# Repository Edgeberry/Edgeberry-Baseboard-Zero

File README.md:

The **Edgeberry Zero** provides essential additional functionality for deploying the Raspberry Pi Zero as an IoT edge device in a real-world environment.

- **12 to 24VDC input power supply** for reliably powering the device with up to 3A at 5V.
- **Indicators and button** for providing status feedback and device interaction
- **Expansion slot** for application-specific Edgeberry Hardware Cartridges
- **Robust enclosure** for withstanding the environmental challenges of the real world

<br/>
<br clear="right"/>

## Edgeberry Device Software
For using your Edgeberry hardware with the Edgeberry ecosystem (e.g. the Edgeberry Dashboard), you'll need to install the [Edgeberry Device Software](https://github.com/Edgeberry/Edgeberry/). Follow [these installation steps](https://github.com/Edgeberry/Edgeberry?tab=readme-ov-file#installation). If you have different plans with this board, this software is not required for correct operation of any of its hardware components.

## Enclosure
The enclosure, designed in FreeCAD, protects the device from the challenges of the physical world.

1) Faceplate front
2) Enclosure
3) Faceplate back
4) Sticker
5) Mounting groove

<br clear="left"/>

## (re)Writing the EEPROM
>[!important]
>**When you purchased the Edgeberry Hardware, the manufacturer has written the EEPROM**. If you are the manufacturer, or you're hacking your Edgeberry board, then continue with the following steps.

1) Close the `write protection` jumper (JP1) on the Edgeberry Hardware to enable writing the EEPROM
2) Download and build the [Raspberry Pi Hat eeprom utils](https://github.com/raspberrypi/hats) on your device 
3) Make the EEPROM file from the eeprom_settings.txt using `eepmake` <br> e.g. `$ ./eepmake eeprom_settings.txt edgeberry.eep`
4) Flash the EEPROM using `eepflash.sh` <br> e.g. `$ sudo ./eepflash -w -t=24c256 -f=edgeberry.eep`
5) Now `reboot` the device and check the device tree for your hat's settings <br> e.g. `$ cat /proc/device-tree/hat/vendor`)

## License & Collaboration
**Copyright© 2025 Sanne 'SpuQ' Santens**. This project is released under the [**CERN OHL-W**](./LICENSE.txt) license. The [Rules & Guidelines](https://github.com/Edgeberry/.github/blob/main/brand/Edgeberry_Trademark_Rules_and_Guidelines.md) apply to the usage of the Edgeberry™ brand.

### Collaboration

If you'd like to contribute to this project, please follow these guidelines:
1. Fork the repository and create your branch from `main`.
2. Make your changes and ensure they adhere to the project's design style and conventions.
3. Test your changes thoroughly.
4. Ensure your commits are descriptive and well-documented.
5. Open a pull request, describing the changes you've made and the problem or feature they address.

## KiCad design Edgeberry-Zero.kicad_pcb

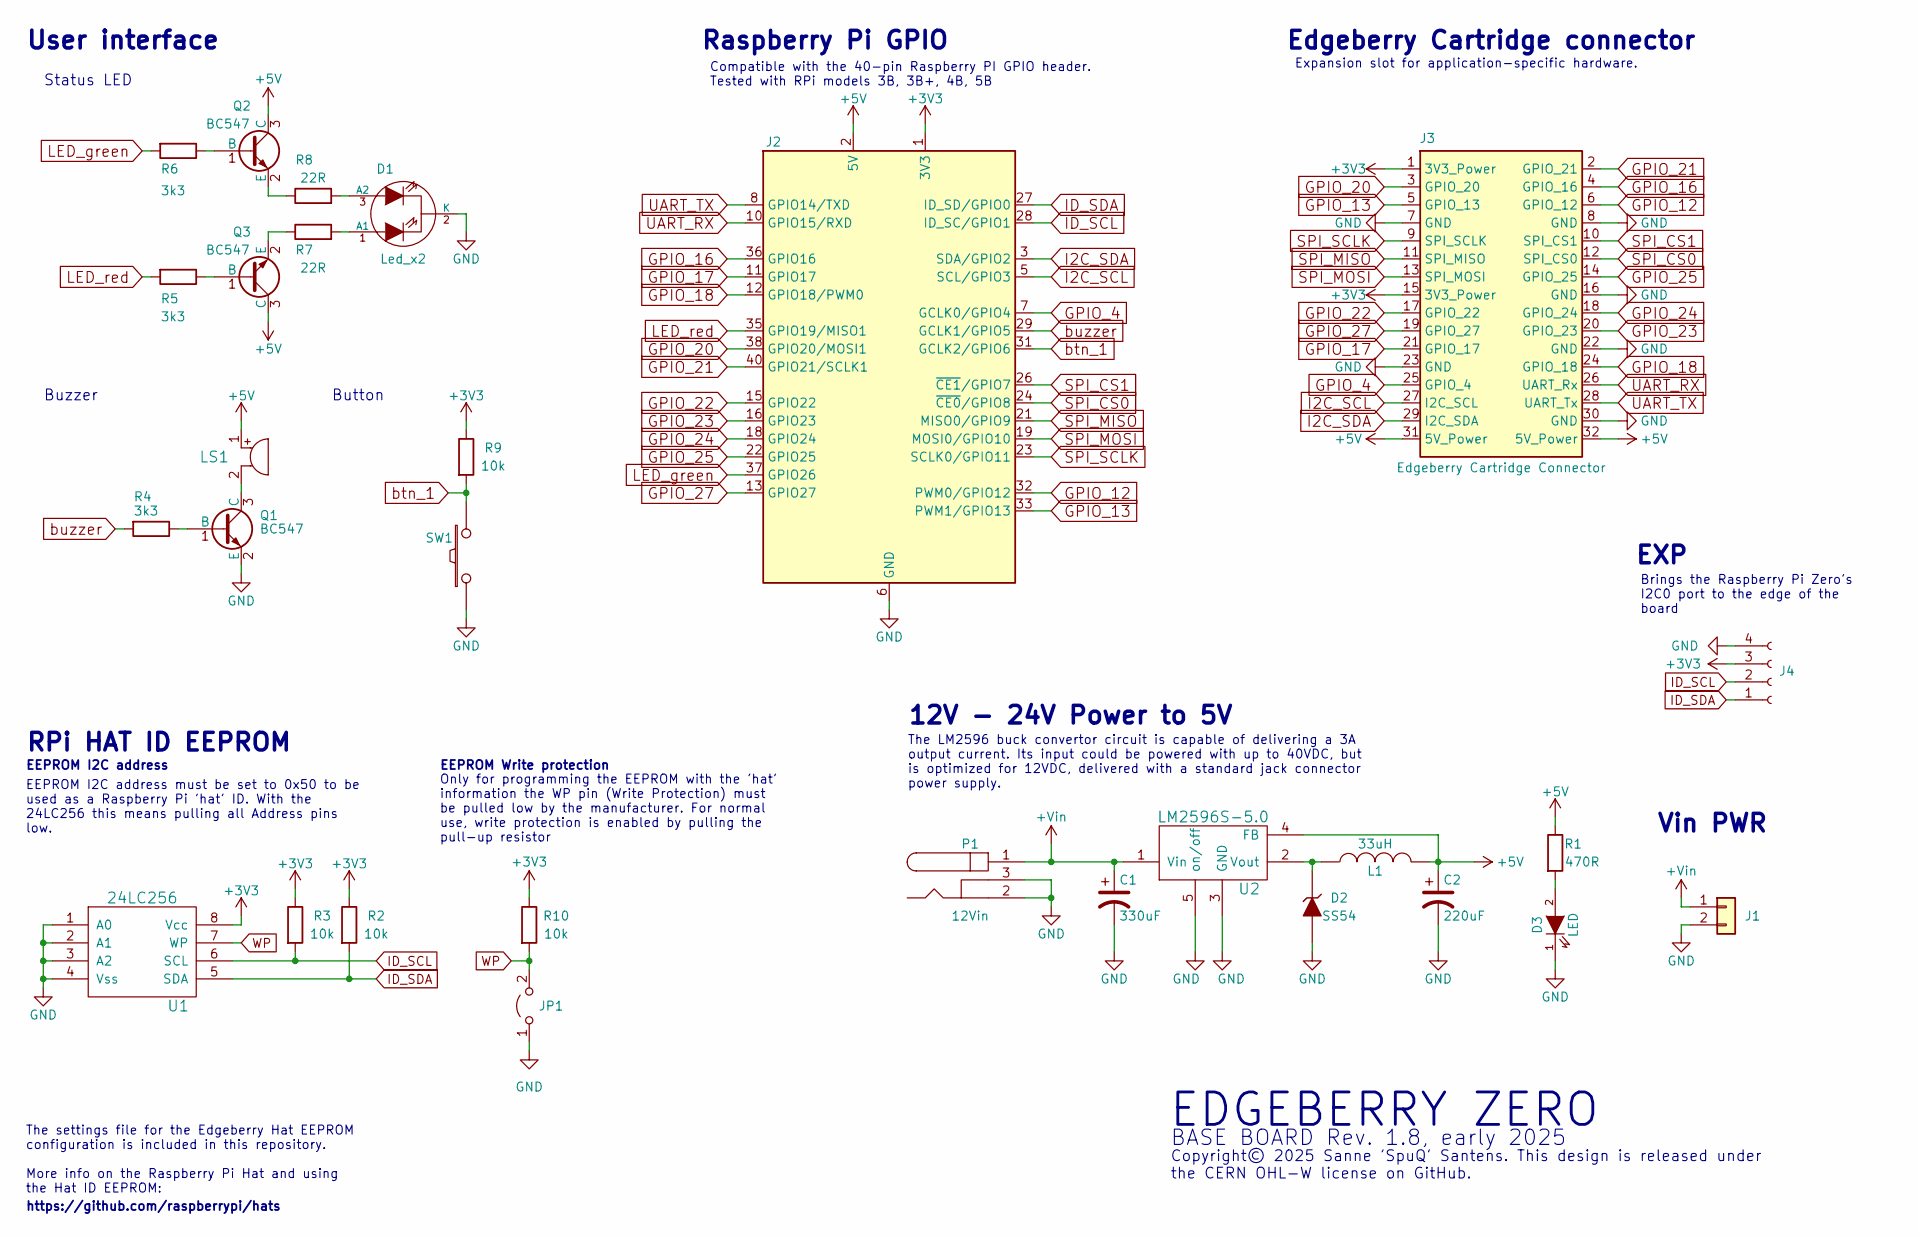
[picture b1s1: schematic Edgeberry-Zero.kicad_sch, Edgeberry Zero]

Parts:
C1: 330uF; c_elec_8x10
C2: 220uF; c_elec_8x10
D1: Led_x2; bicolor_LED_right_angle
D2: SS54; D_SMA
D3: LED; LED_0805_2012Metric
J1: Molex_KK_1x02_P2.54mm; Molex_KK-254_AE-6410-02A_1x02_P2.54mm_Vertical
J2: Raspberry_Pi_2_3; PinSocket_2x20_P2.54mm_Vertical
J3: Edgeberry Cartridge Connector; PinSocket_2x16_P2.54mm_Horizontal
J4: Conn_01x04_Socket; PinSocket_1x04_P2.00mm_Horizontal
JP1: Jumper_2_Open; PinHeader_1x02_P2.54mm_Vertical
L1: 33uH; SELF-WE-PD-XXL
LS1: Buzzer; Buzzer_12x9.5RM7.6
P1: 12Vin; BarrelJack_Horizontal
Q1, Q2, Q3: BC547; SOT-23
R1: 470R; R_0805_2012Metric
R2, R3, R9, R10: 10k; R_0805_2012Metric
R4, R5, R6: 3k3; R_0805_2012Metric
R7, R8: 22R; R_0805_2012Metric
SW1: SW_PUSH; tactile_switch_vertical
U1: 24LC256; SOIC_8
U2: LM2596S-5.0; TO-263-5_TabPin3

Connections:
+3V3: J2.1 (3V3), J2.17 (3V3), J3.1 (3V3_Power), J3.15 (3V3_Power), J4.3, R2.1, R3.1, R9.1, R10.1, U1.8 (Vcc)
+5V: C2.1, J2.2 (5V), J2.4 (5V), J3.31 (5V_Power), J3.32 (5V_Power), L1.2, LS1.1, Q2.3 (C), Q3.3 (C), R1.1, U2.4 (FB)
+Vin: C1.1, J1.1, P1.1, U2.1 (Vin)
GND: C1.2, C2.2, D1.2 (K), D2.2 (A), D3.1 (K), J1.2, J2.6 (GND), J2.9 (GND), J2.14 (GND), J2.20 (GND), J2.25 (GND), J2.30 (GND), J2.34 (GND), J2.39 (GND), J3.7 (GND), J3.8 (GND), J3.16 (GND), J3.22 (GND), J3.23 (GND), J3.30 (GND), J4.4, JP1.1 (A), P1.2, P1.3, Q1.2 (E), SW1.1, U1.1 (A0), U1.2 (A1), U1.3 (A2), U1.4 (Vss), U2.3 (GND), U2.5 (on/off)
GPIO_4: J2.7 (GCLK0/GPIO4), J3.25 (GPIO_4)
GPIO_12: J2.32 (PWM0/GPIO12), J3.6 (GPIO_12)
GPIO_13: J2.33 (PWM1/GPIO13), J3.5 (GPIO_13)
GPIO_16: J2.36 (GPIO16), J3.4 (GPIO_16)
GPIO_17: J2.11 (GPIO17), J3.21 (GPIO_17)
GPIO_18: J2.12 (GPIO18/PWM0), J3.24 (GPIO_18)
GPIO_20: J2.38 (GPIO20/MOSI1), J3.3 (GPIO_20)
GPIO_21: J2.40 (GPIO21/SCLK1), J3.2 (GPIO_21)
GPIO_22: J2.15 (GPIO22), J3.17 (GPIO_22)
GPIO_23: J2.16 (GPIO23), J3.20 (GPIO_23)
GPIO_24: J2.18 (GPIO24), J3.18 (GPIO_24)
GPIO_25: J2.22 (GPIO25), J3.14 (GPIO_25)
GPIO_27: J2.13 (GPIO27), J3.19 (GPIO_27)
I2C_SCL: J2.5 (SCL/GPIO3), J3.27 (I2C_SCL)
I2C_SDA: J2.3 (SDA/GPIO2), J3.29 (I2C_SDA)
ID_SCL: J2.28 (ID_SC/GPIO1), J4.2, R3.2, U1.6 (SCL)
ID_SDA: J2.27 (ID_SD/GPIO0), J4.1, R2.2, U1.5 (SDA)
LED_green: J2.37 (GPIO26), R6.2
LED_red: J2.35 (GPIO19/MISO1), R5.2
unnamed: D1.1 (A1), R7.2
unnamed: D1.3 (A2), R8.2
unnamed: D2.1 (K), L1.1, U2.2 (Vout)
unnamed: D3.2 (A), R1.2
unnamed: Q1.1 (B), R4.1
unnamed: LS1.2, Q1.3 (C)
unnamed: Q2.1 (B), R6.1
unnamed: Q2.2 (E), R8.1
unnamed: Q3.1 (B), R5.1
unnamed: Q3.2 (E), R7.1
SPI_CS0: J2.24 (~CE0/GPIO8), J3.12 (SPI_CS0)
SPI_CS1: J2.26 (~CE1/GPIO7), J3.10 (SPI_CS1)
SPI_MISO: J2.21 (MISO0/GPIO9), J3.11 (SPI_MISO)
SPI_MOSI: J2.19 (MOSI0/GPIO10), J3.13 (SPI_MOSI)
SPI_SCLK: J2.23 (SCLK0/GPIO11), J3.9 (SPI_SCLK)
UART_RX: J2.10 (GPIO15/RXD), J3.26 (UART_Rx)
UART_TX: J2.8 (GPIO14/TXD), J3.28 (UART_Tx)
WP: JP1.2 (B), R10.2, U1.7 (WP)
btn_1: J2.31 (GCLK2/GPIO6), R9.2, SW1.2
buzzer: J2.29 (GCLK1/GPIO5), R4.2

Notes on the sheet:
Copyright© 2025 Sanne 'SpuQ' Santens. This design is released under the CERN OHL-W license on GitHub.
Button
BASE BOARD Rev. 1.8, early 2025
EEPROM I2C address must be set to 0x50 to be used as a Raspberry Pi 'hat' ID. With the 24LC256 this means pulling all Address pins low.
User interface
12V - 24V Power to 5V
EEPROM Write protection
Raspberry Pi GPIO
Vin PWR
Brings the Raspberry Pi Zero's I2C0 port to the edge of the board
RPi HAT ID EEPROM
https://github.com/raspberrypi/hats
The settings file for the Edgeberry Hat EEPROM configuration is included in this repository. More info on the Raspberry Pi Hat and using the Hat ID EEPROM:
The LM2596 buck convertor circuit is capable of delivering a 3A output current. Its input could be powered with up to 40VDC, but is optimized for 12VDC, delivered with a standard jack connector power supply.
EXP
Only for programming the EEPROM with the 'hat' information the WP pin (Write Protection) must be pulled low by the manufacturer. For normal use, write protection is enabled by pulling the pull-up resistor
Buzzer
Status LED
EDGEBERRY ZERO
Expansion slot for application-specific hardware.
Edgeberry Cartridge connector
EEPROM I2C address
Compatible with the 40-pin Raspberry PI GPIO header. Tested with RPi models 3B, 3B+, 4B, 5B

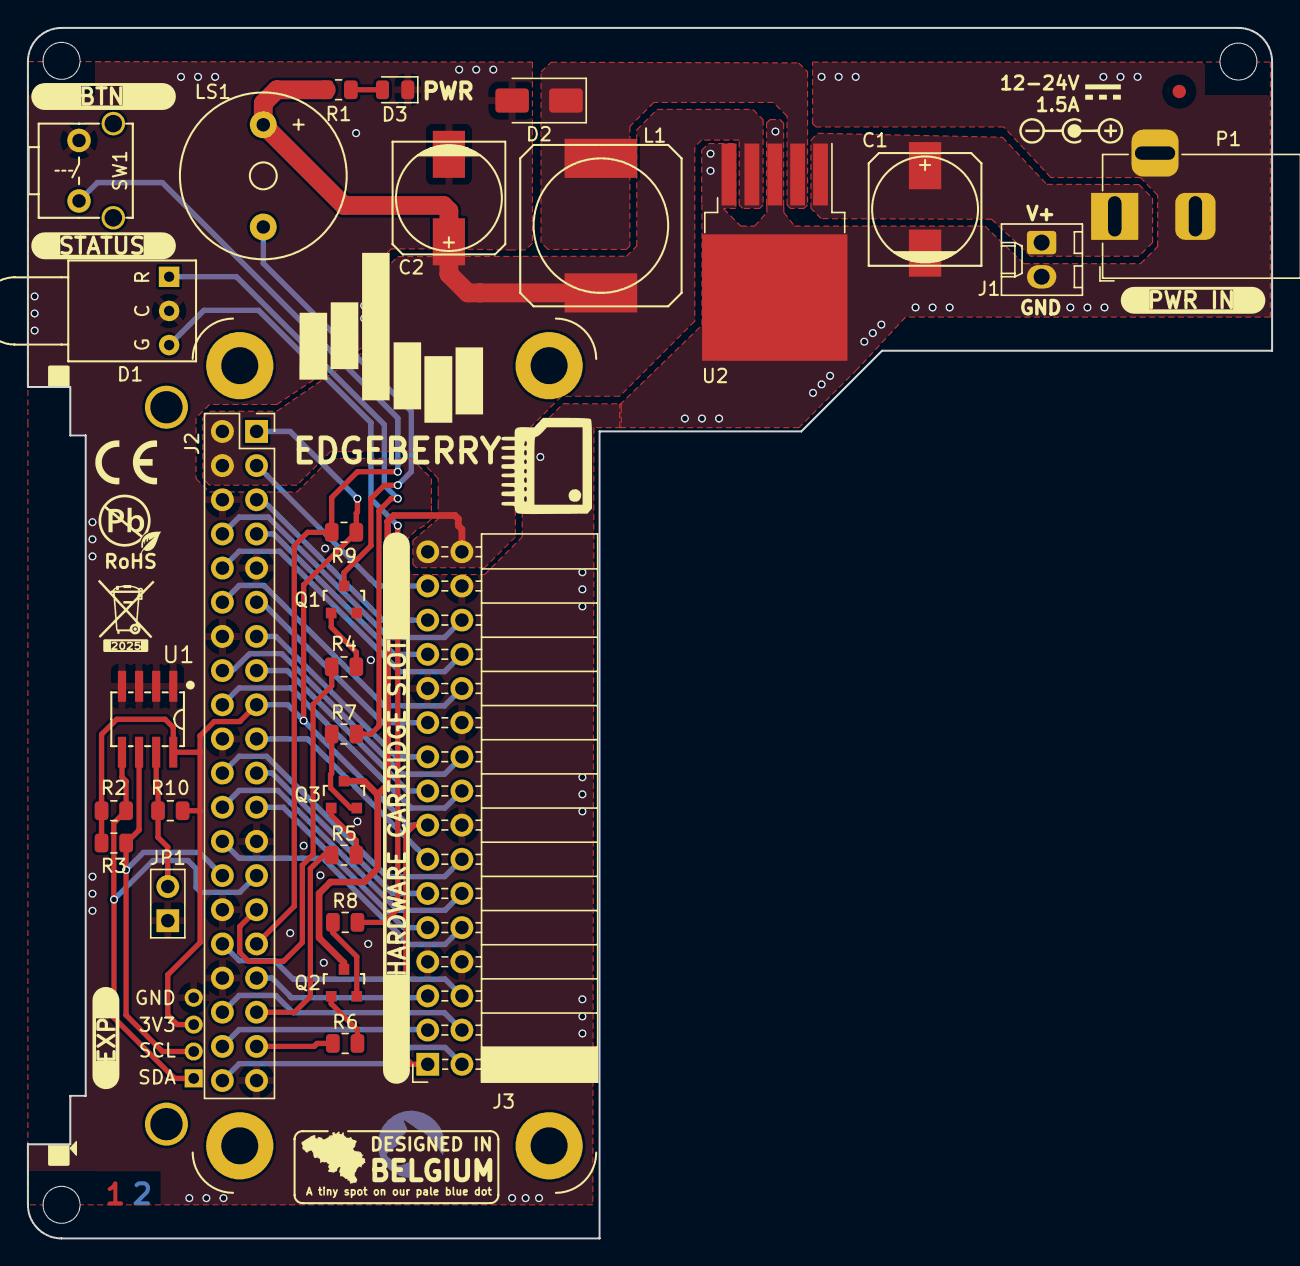
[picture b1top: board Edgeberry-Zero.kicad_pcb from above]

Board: 2 copper layers, 92.5 x 90.0 mm, 29 parts (1 on the bottom side), 43 nets.

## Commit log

2025-02-12 Edgeberry Zero concept
2025-02-12 Even smaller
2025-02-12 New banner
2025-02-12 Component arrangement + Mechanical dimensions
2025-02-13 Enclosure updates
2025-02-13 ReadMe: update introduction text
2025-02-13 cleanup
2025-02-27 Finished design
2025-02-27 Enclosure: logo
2025-03-16 uniformity
2025-03-20 Documentation: Enclosure mechanical drawing
2025-03-20 Documentation: Enclosure mechanical drawing pdf format
2025-04-26 Improvements: C2, J4 (ext)
2025-05-07 Rev 1.8
2025-05-07 Update EEPROM settings
2025-05-07 Rendering for rev 8.1
2026-05-08 Enclosure directory
2026-05-08 Enclosure revision
2026-05-13 Enclosure Rev 2.1
2026-05-13 Updated enclosure implementation
2026-05-13 Documentation update
2026-05-13 Enclosure: Logo sticker template
2026-05-13 Enclosure: Mechanical Drawing
2026-05-13 ReadMe: Enclosure section concept
2026-05-13 Docs: Enclosure drawing cleanup
2026-05-13 ReadMe: Enclosure drawing cleanup
2026-05-13 Enclosure: mounting groove doc
2026-05-13 Organization improvements
2026-06-11 Enclosure: Faceplate back improvement
